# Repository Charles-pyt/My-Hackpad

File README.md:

# My-Hackpad
I made this projet through a HackClub workshop at home. With a custom PCB I can make my own keyboard with shortcut for exemple. Here are some images of the project:
# Schematic

# Circuit

# Box

# Top

# Inside

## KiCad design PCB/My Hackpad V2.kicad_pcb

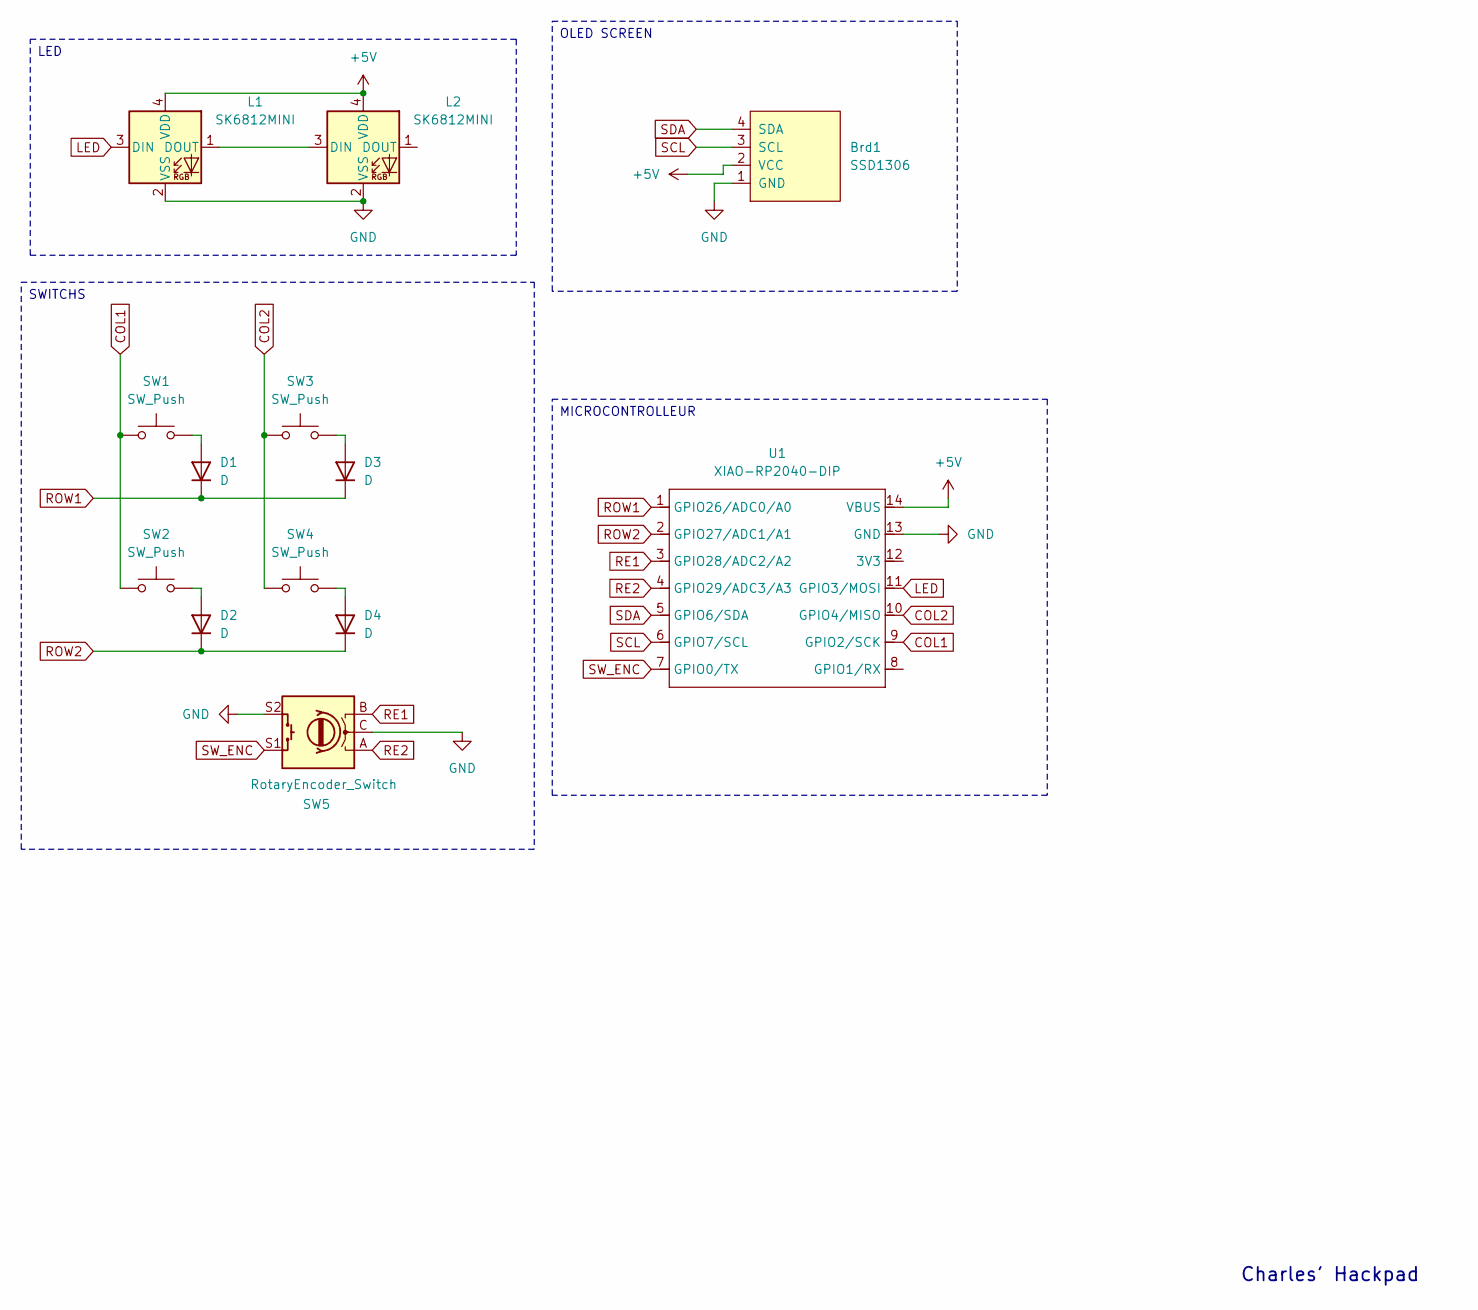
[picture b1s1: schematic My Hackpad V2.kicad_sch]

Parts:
Brd1: SSD1306; SSD1306-0.91-OLED-4pin-128x32
D1, D2, D3, D4: D; D_DO-35_SOD27_P7.62mm_Horizontal
L1, L2: SK6812MINI; LED_SK6812MINI_PLCC4_3.5x3.5mm_P1.75mm
SW1, SW2, SW3, SW4: SW_Push; SW_Cherry_MX_1.00u_PCB
SW5: RotaryEncoder_Switch; RotaryEncoder_Alps_EC11E-Switch_Vertical_H20mm
U1: XIAO-RP2040-DIP

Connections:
+5V: Brd1.2 (VCC), L1.4 (VDD), L2.4 (VDD), U1.14 (VBUS)
COL1: SW1.1, SW2.1, U1.9 (GPIO2/SCK)
COL2: SW3.1, SW4.1, U1.10 (GPIO4/MISO)
GND: Brd1.1 (GND), L1.2 (VSS), L2.2 (VSS), SW5.C, SW5.S2, U1.13 (GND)
LED: L1.3 (DIN), U1.11 (GPIO3/MOSI)
unnamed: D1.2 (A), SW1.2
unnamed: D2.2 (A), SW2.2
unnamed: D3.2 (A), SW3.2
unnamed: D4.2 (A), SW4.2
unnamed: L1.1 (DOUT), L2.3 (DIN)
RE1: SW5.B, U1.3 (GPIO28/ADC2/A2)
RE2: SW5.A, U1.4 (GPIO29/ADC3/A3)
ROW1: D1.1 (K), D3.1 (K), U1.1 (GPIO26/ADC0/A0)
ROW2: D2.1 (K), D4.1 (K), U1.2 (GPIO27/ADC1/A1)
SCL: Brd1.3 (SCL), U1.6 (GPIO7/SCL)
SDA: Brd1.4 (SDA), U1.5 (GPIO6/SDA)
SW_ENC: SW5.S1, U1.7 (GPIO0/TX)

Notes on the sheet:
Charles' Hackpad
OLED SCREEN
MICROCONTROLLEUR
LED
SWITCHS

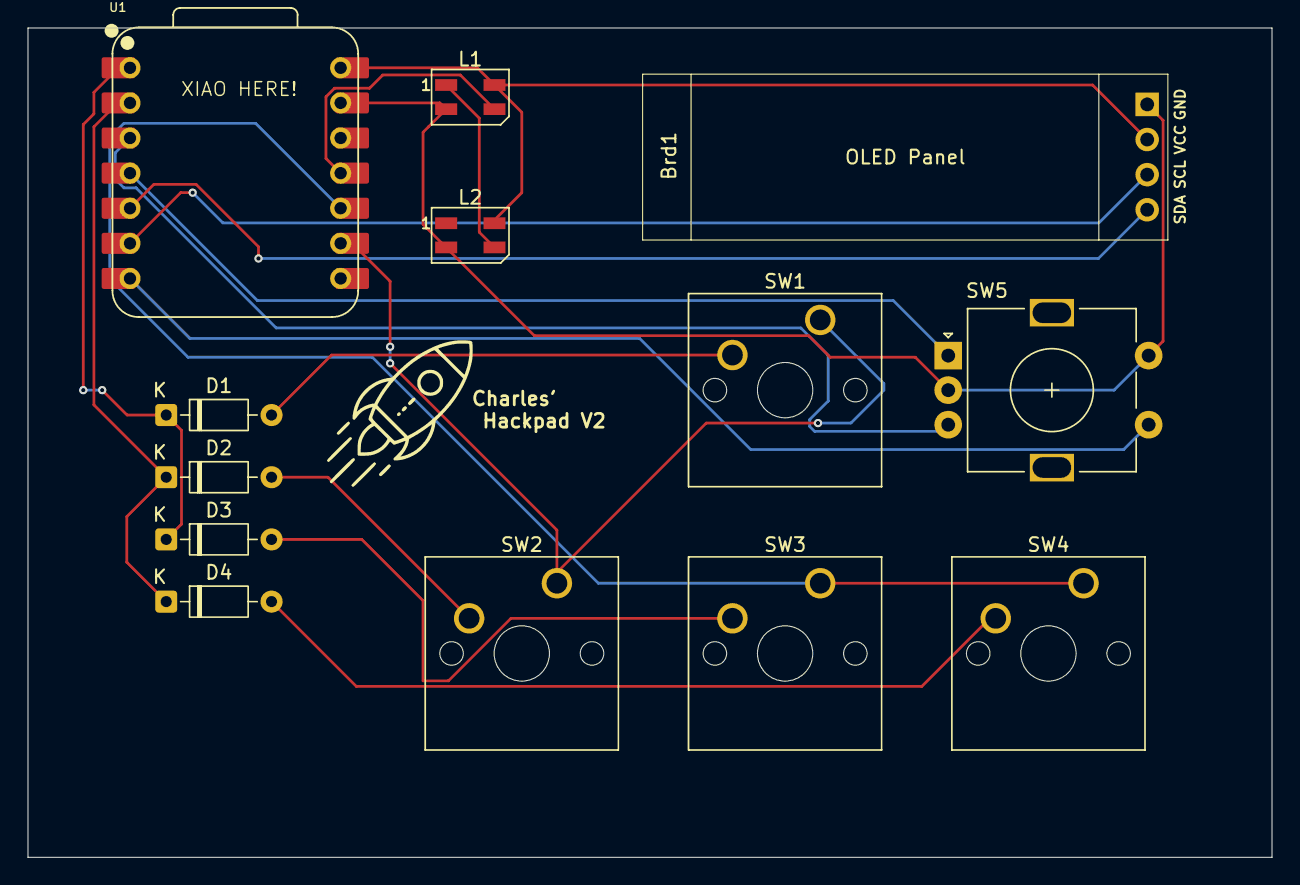
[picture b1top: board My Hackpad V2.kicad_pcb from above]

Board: 2 copper layers, 90.0 x 60.0 mm, 13 parts (0 on the bottom side), 17 nets.

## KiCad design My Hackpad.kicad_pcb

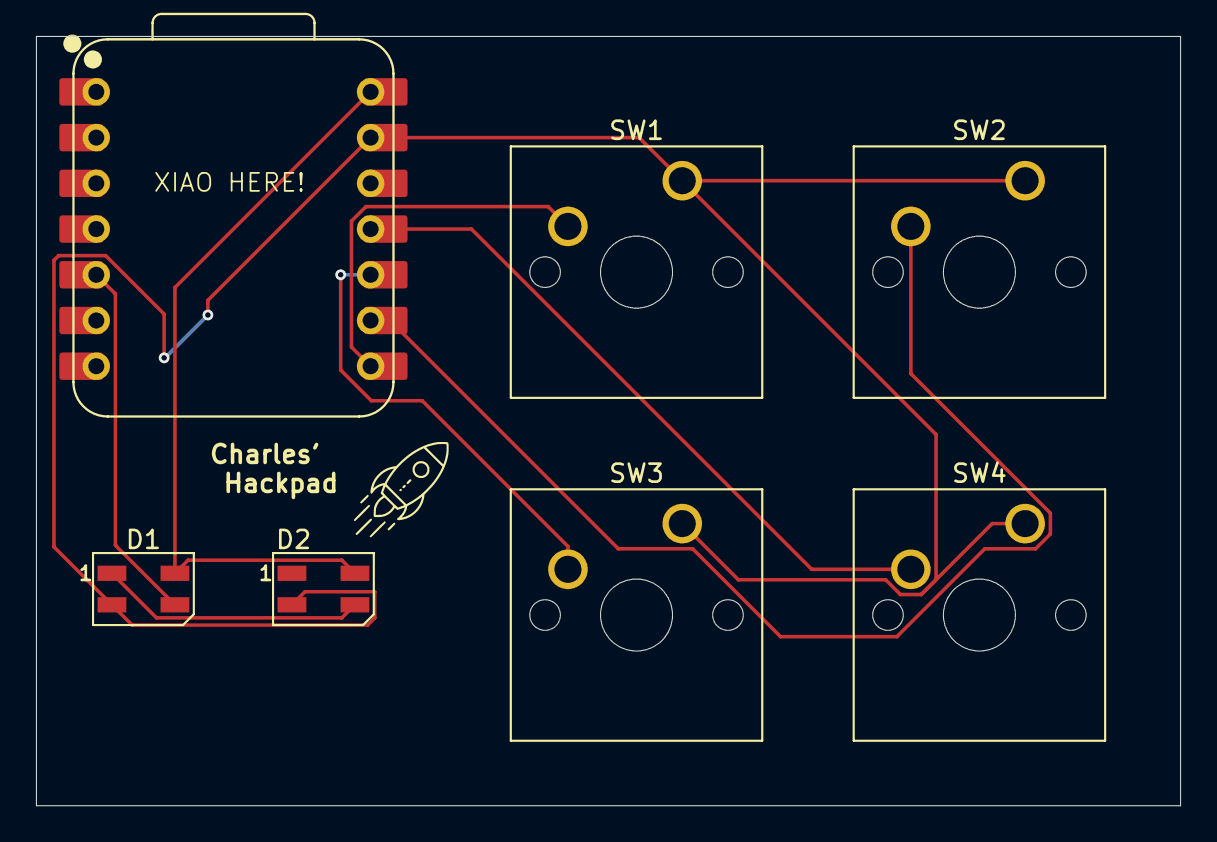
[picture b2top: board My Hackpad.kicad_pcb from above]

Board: 2 copper layers, 63.6 x 42.7 mm, 7 parts (0 on the bottom side), 8 nets.

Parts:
D1, D2: SK6812MINI; LED_SK6812MINI_PLCC4_3.5x3.5mm_P1.75mm
SW1, SW2, SW3, SW4: SW_Push; SW_Cherry_MX_1.00u_PCB
U1: XIAO-RP2040-DIP

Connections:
+5V: D1.4 (VDD), D2.4 (VDD), U1.14 (VBUS)
GND: D1.2 (VSS), D2.2 (VSS), SW1.1, SW2.1, SW3.1, SW4.1, U1.13 (GND)
unnamed: D1.3 (DIN), U1.5 (GPIO6/SDA)
unnamed: D1.1 (DOUT), D2.3 (DIN)
unnamed: SW1.2, U1.8 (GPIO1/RX)
unnamed: SW2.2, U1.9 (GPIO2/SCK)
unnamed: SW4.2, U1.11 (GPIO3/MOSI)
unnamed: SW3.2, U1.10 (GPIO4/MISO)

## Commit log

2025-12-14 Enhance README with project images and details
    Added images and sections for schematic and circuit.
2025-12-17 Add STL files and move images to images/ directory
    Added Box.stl and Top.stl to the STL directory. Moved all image files into the images/ directory for better organization.
2025-12-17 Reorganize PCB files and add STEP models
    Moved KiCad project files into a new 'PCB' directory and renamed output files for clarity. Added STEP models for enclosure parts and removed obsolete STL files.
